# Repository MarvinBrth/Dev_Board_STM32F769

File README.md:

# Dev_Board_STM32F769
## Feature
- STM32F769BIT6
- OTG USB C FS
- OTG USB C HS
- DRAM
- DSI_Interface
- EMMC
### Infos
- Created with Kicad
- 6 Layer
- 5 x 5 cm
- Manufactorer: JLCPCB
- PCBA
  
## Blockdiagramm:

## Supply:

## STM32F769BIT6:

## USB_C_FS_OTG:

## USB_C_HS_OTG:

## EMMC:

## DSI_Interface:

## SDRAM:

## Layout:

## 3D-Model:

## Real life

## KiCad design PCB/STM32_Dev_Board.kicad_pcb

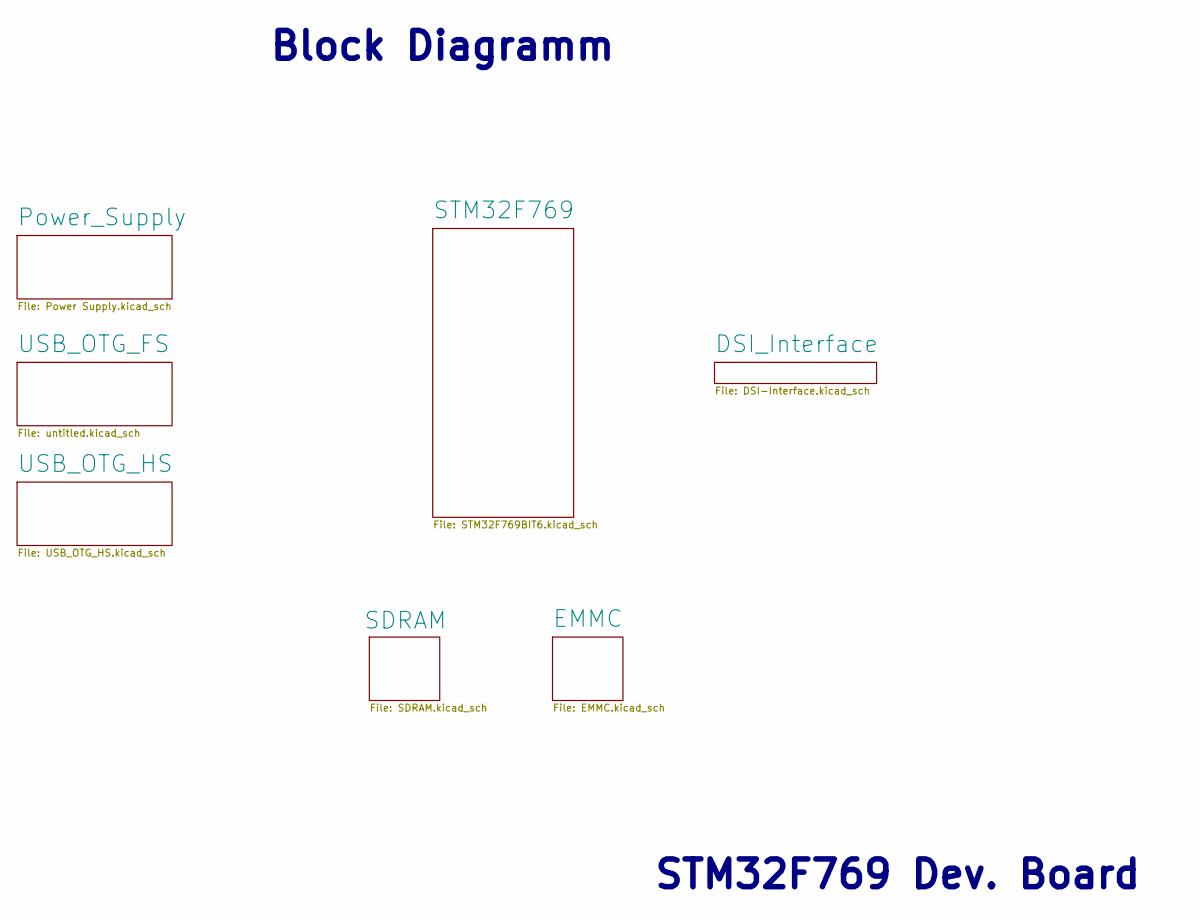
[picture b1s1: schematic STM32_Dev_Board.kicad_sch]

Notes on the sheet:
STM32F769 Dev. Board
Block Diagramm

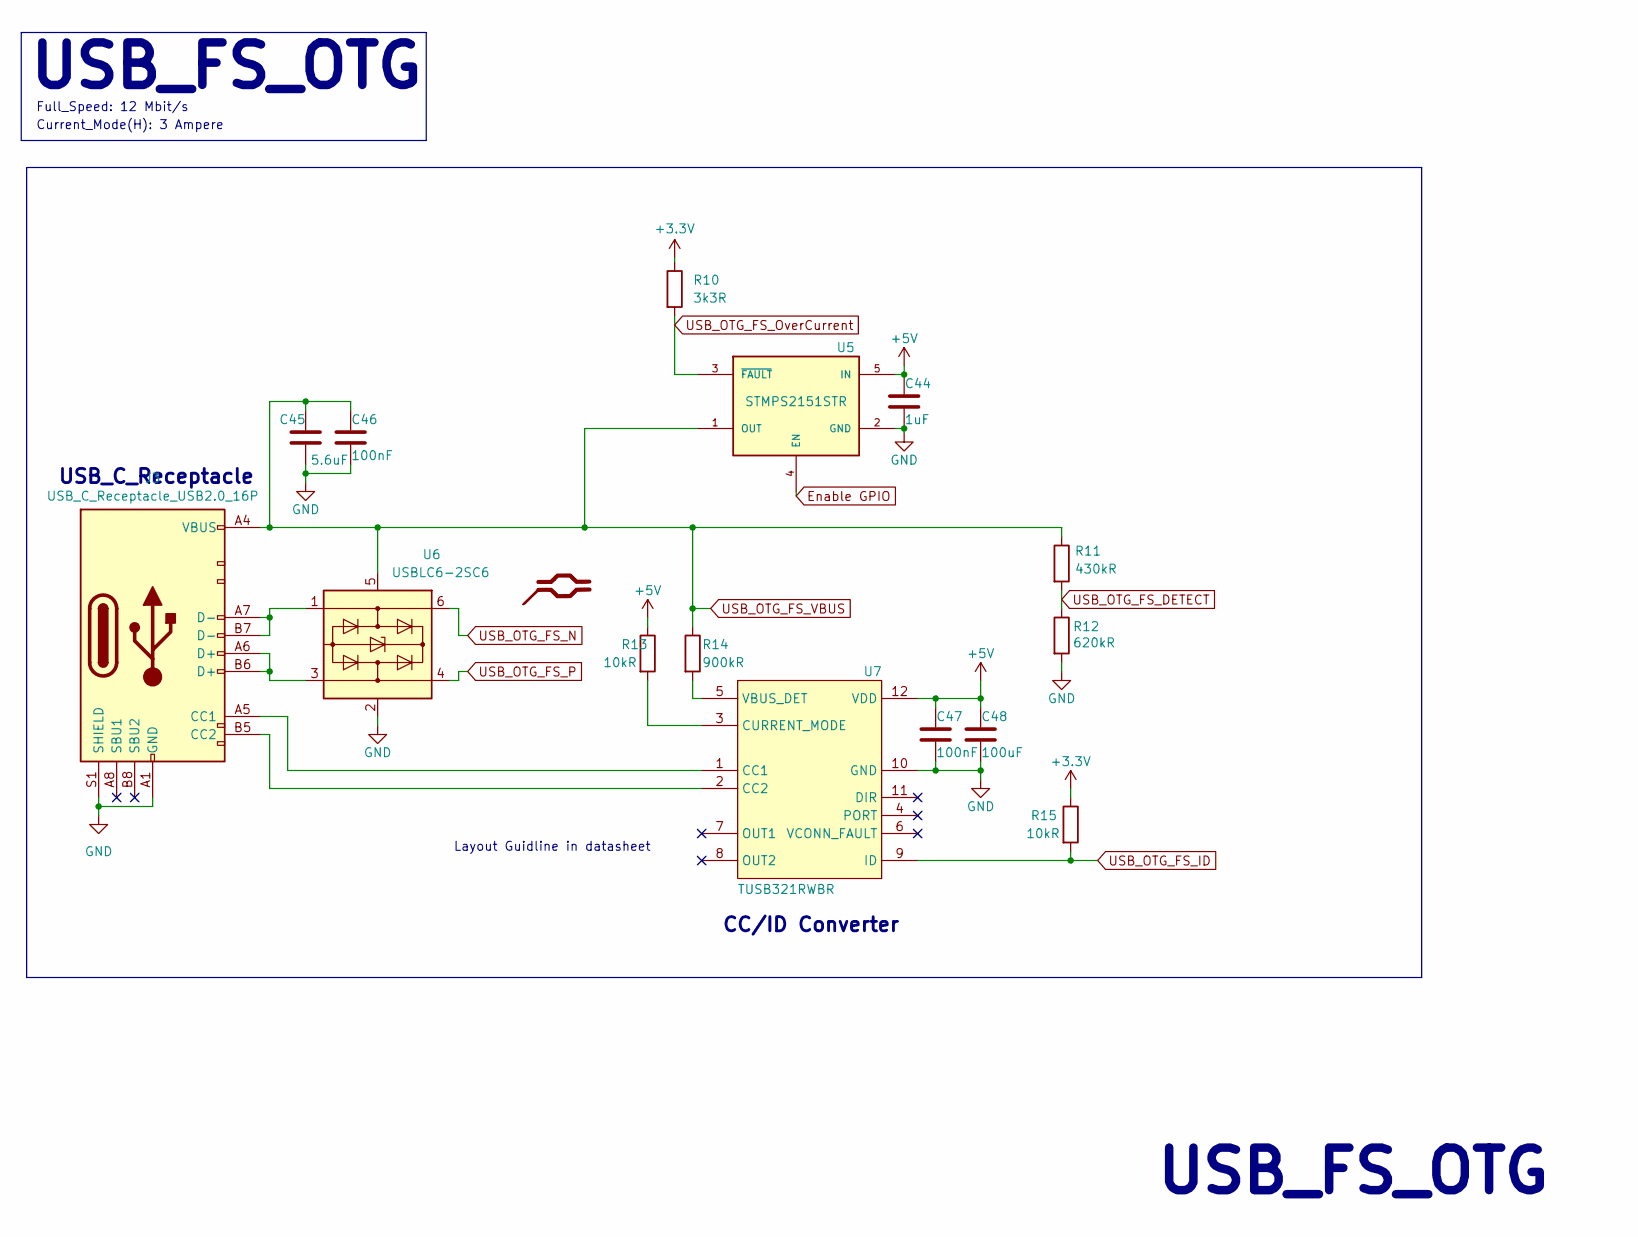
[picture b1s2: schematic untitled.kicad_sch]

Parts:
C44: 1uF; C_0603_1608Metric
C45: 5.6uF; C_0603_1608Metric
C46, C47: 100nF; C_0402_1005Metric
C48: 100uF; C_0805_2012Metric
J3: USB_C_Receptacle_USB2.0_16P; GT-USB-7047B_JLCPCB
R10: 3k3R; R_0402_1005Metric
R11: 430kR; R_0402_1005Metric
R12: 620kR; R_0402_1005Metric
R13, R15: 10kR; R_0402_1005Metric
R14: 900kR; R_0402_1005Metric
U5: STMPS2151STR; STMPS; PARTREV 7
U6: USBLC6-2SC6; SOT-23-6
U7: TUSB321RWBR

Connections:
+5V: C44.1, C47.1, C48.1, R13.1, U5.5 (IN), U7.12 (VDD); also elsewhere on the board
Enable GPIO: U5.4 (EN); also elsewhere on the board
GND: C44.2, C45.2, C46.2, C47.2, C48.2, J3.A1 (GND), J3.A12 (GND), J3.B1 (GND), J3.B12 (GND), J3.S1 (SHIELD), R12.2, U5.2 (GND), U6.2 (GND), U7.10 (GND); also elsewhere on the board
unnamed: J3.A5 (CC1), U7.1 (CC1)
unnamed: J3.B5 (CC2), U7.2 (CC2)
unnamed: J3.A6 (D+), J3.B6 (D+), U6.3 (I/O2)
unnamed: J3.A7 (D-), J3.B7 (D-), U6.1 (I/O1)
unnamed: R13.2, U7.3 (CURRENT_MODE)
unnamed: R14.2, U7.5 (VBUS_DET)
USB_OTG_FS_DETECT: R11.2, R12.1; also elsewhere on the board
USB_OTG_FS_ID: R15.2, U7.9 (ID); also elsewhere on the board
USB_OTG_FS_N: U6.6 (I/O1); also elsewhere on the board
USB_OTG_FS_OverCurrent: R10.2, U5.3 (~FAULT); also elsewhere on the board
USB_OTG_FS_P: U6.4 (I/O2); also elsewhere on the board
USB_OTG_FS_VBUS: C45.1, C46.1, J3.A4 (VBUS), J3.A9 (VBUS), J3.B4 (VBUS), J3.B9 (VBUS), R11.1, R14.1, U5.1 (OUT), U6.5 (VBUS); also elsewhere on the board
VDDSDMMC_STM32: R10.1, R15.1; also elsewhere on the board

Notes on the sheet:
Full_Speed: 12 Mbit/s
USB_FS_OTG
CC/ID Converter
Current_Mode(H): 3 Ampere
USB_C_Receptacle
Layout Guidline in datasheet

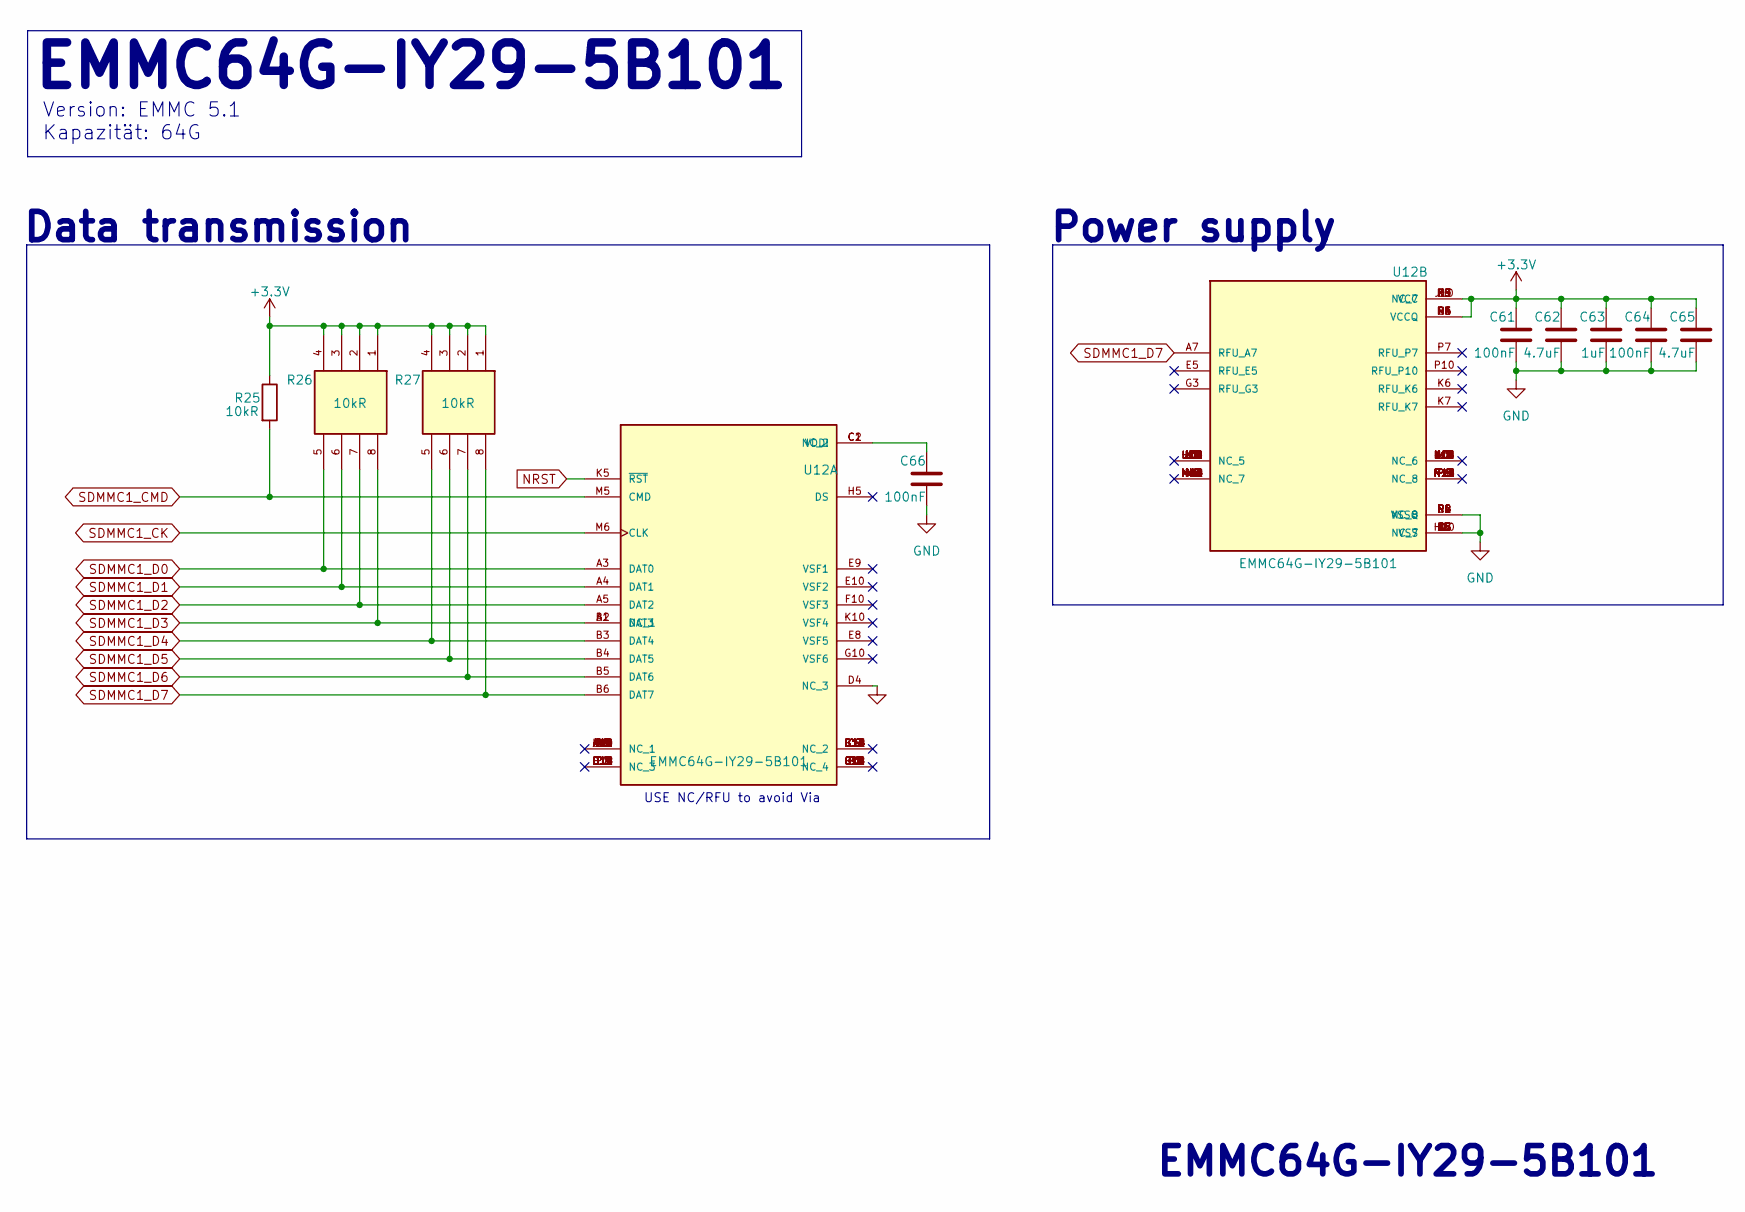
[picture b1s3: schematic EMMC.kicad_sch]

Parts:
C61, C64, C66: 100nF; C_0402_1005Metric
C62, C65: 4.7uF; C_0402_1005Metric
C63: 1uF; C_0402_1005Metric
R25: 10kR; R_0402_1005Metric
R26, R27: 10kR; Widerstandsarray_1; PARTREV 1-Mar-20
U12: EMMC64G-IY29-5B101; EMMC; PARTREV N/A

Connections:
GND: C61.2, C62.2, C63.2, C64.2, C65.2, C66.2, U12.A6 (VSS), U12.C4 (VSSQ), U12.D4 (NC_3), U12.E7 (VSS), U12.G5 (VSS), U12.H10 (VSS), U12.J5 (VSS), U12.K8 (VSS), U12.N2 (VSSQ), U12.N5 (VSSQ), U12.N6 (NC_7), U12.P2 (NC_8), U12.P4 (VSSQ), U12.P6 (VSSQ); also elsewhere on the board
NRST: U12.K5 (~RST); also elsewhere on the board
unnamed: C66.1, U12.C1 (NC_2), U12.C2 (VDDI)
SDMMC1_CK: U12.M6 (CLK); also elsewhere on the board
SDMMC1_CMD: R25.2, U12.M5 (CMD); also elsewhere on the board
SDMMC1_D0: R26.5, U12.A3 (DAT0); also elsewhere on the board
SDMMC1_D1: R26.6, U12.A4 (DAT1); also elsewhere on the board
SDMMC1_D2: R26.7, U12.A5 (DAT2); also elsewhere on the board
SDMMC1_D3: R26.8, U12.A1 (NC_1), U12.B2 (DAT3); also elsewhere on the board
SDMMC1_D4: R27.5, U12.A2 (NC_1), U12.B3 (DAT4); also elsewhere on the board
SDMMC1_D5: R27.6, U12.B4 (DAT5), U12.C3 (NC_2), U12.D1 (NC_3), U12.D2 (NC_3), U12.D3 (NC_3); also elsewhere on the board
SDMMC1_D6: R27.7, U12.B5 (DAT6), U12.C5 (NC_2); also elsewhere on the board
SDMMC1_D7: R27.8, U12.A7 (RFU_A7), U12.B6 (DAT7); also elsewhere on the board
VDDSDMMC_STM32: C61.1, C62.1, C63.1, C64.1, C65.1, R25.1, R26.1, R26.2, R26.3, R26.4, R27.1, R27.2, R27.3, R27.4, U12.C6 (VCCQ), U12.E6 (VCC), U12.F5 (VCC), U12.J10 (VCC), U12.K9 (VCC), U12.M4 (VCCQ), U12.N3 (NC_7), U12.N4 (VCCQ), U12.P3 (VCCQ), U12.P5 (VCCQ); also elsewhere on the board

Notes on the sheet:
USE NC/RFU to avoid Via
Data transmission
EMMC64G-IY29-5B101
Version: EMMC 5.1 Kapazität: 64G
Power supply

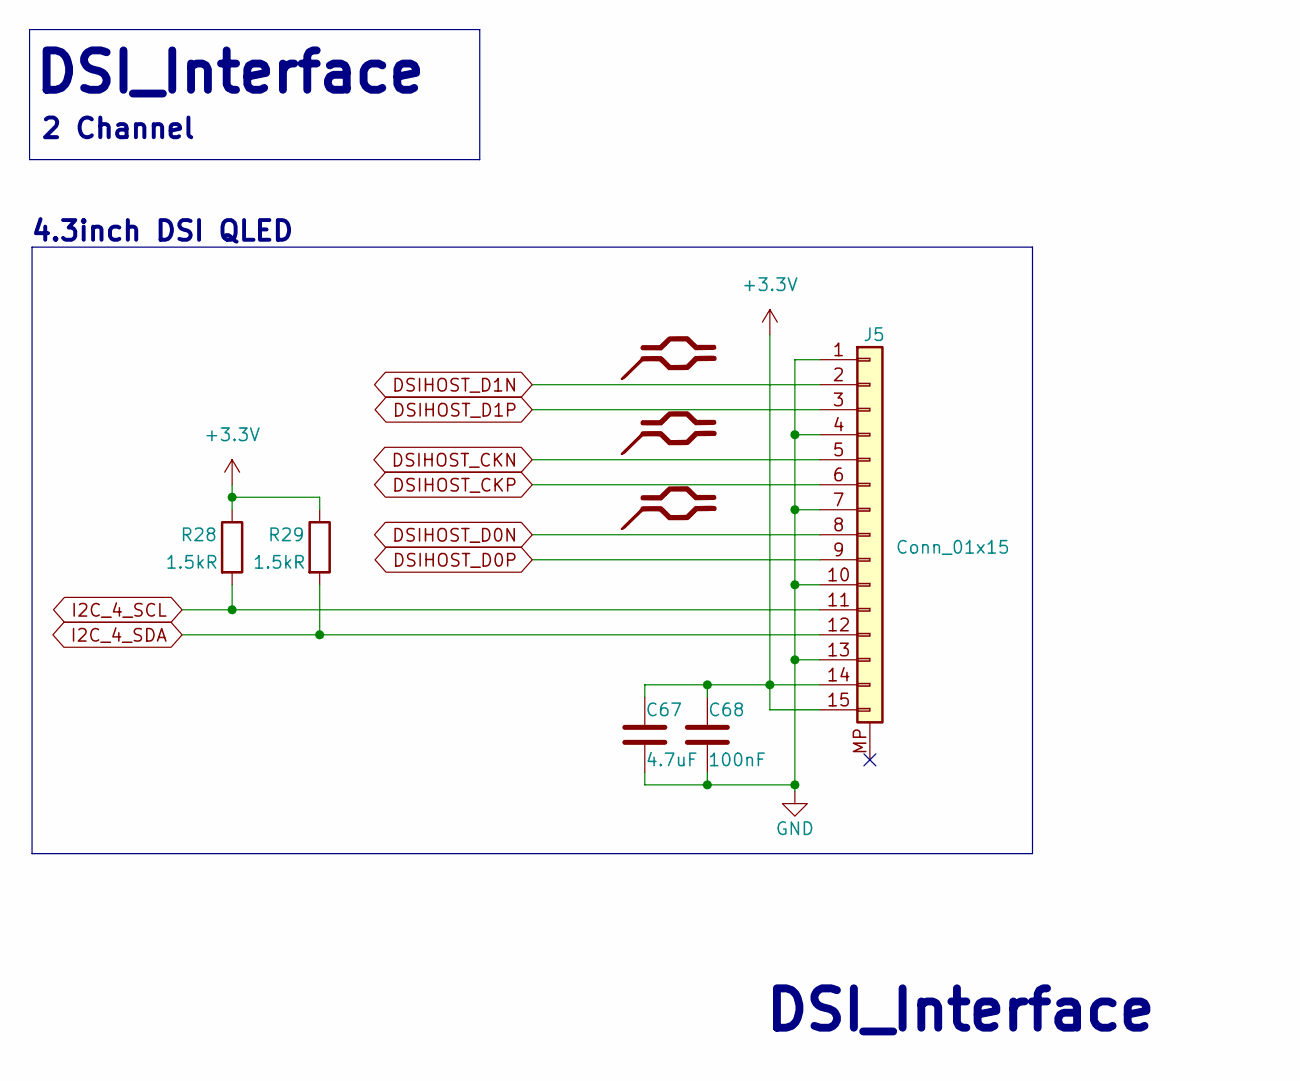
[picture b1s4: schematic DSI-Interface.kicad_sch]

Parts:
C67: 4.7uF; C_0603_1608Metric
C68: 100nF; C_0402_1005Metric
J5: Conn_01x15; TE_1-84952-5_1x15-1MP_P1.0mm_Horizontal
R28, R29: 1.5kR; R_0402_1005Metric

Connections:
DSIHOST_CKN: J5.5; also elsewhere on the board
DSIHOST_CKP: J5.6; also elsewhere on the board
DSIHOST_D0N: J5.8; also elsewhere on the board
DSIHOST_D0P: J5.9; also elsewhere on the board
DSIHOST_D1N: J5.2; also elsewhere on the board
DSIHOST_D1P: J5.3; also elsewhere on the board
GND: C67.2, C68.2, J5.1, J5.4, J5.7, J5.10, J5.13; also elsewhere on the board
I2C_4_SCL: J5.11, R28.2; also elsewhere on the board
I2C_4_SDA: J5.12, R29.2; also elsewhere on the board
VDDSDMMC_STM32: C67.1, C68.1, J5.14, J5.15, R28.1, R29.1; also elsewhere on the board

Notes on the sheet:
DSI_Interface
2 Channel
4.3inch DSI QLED

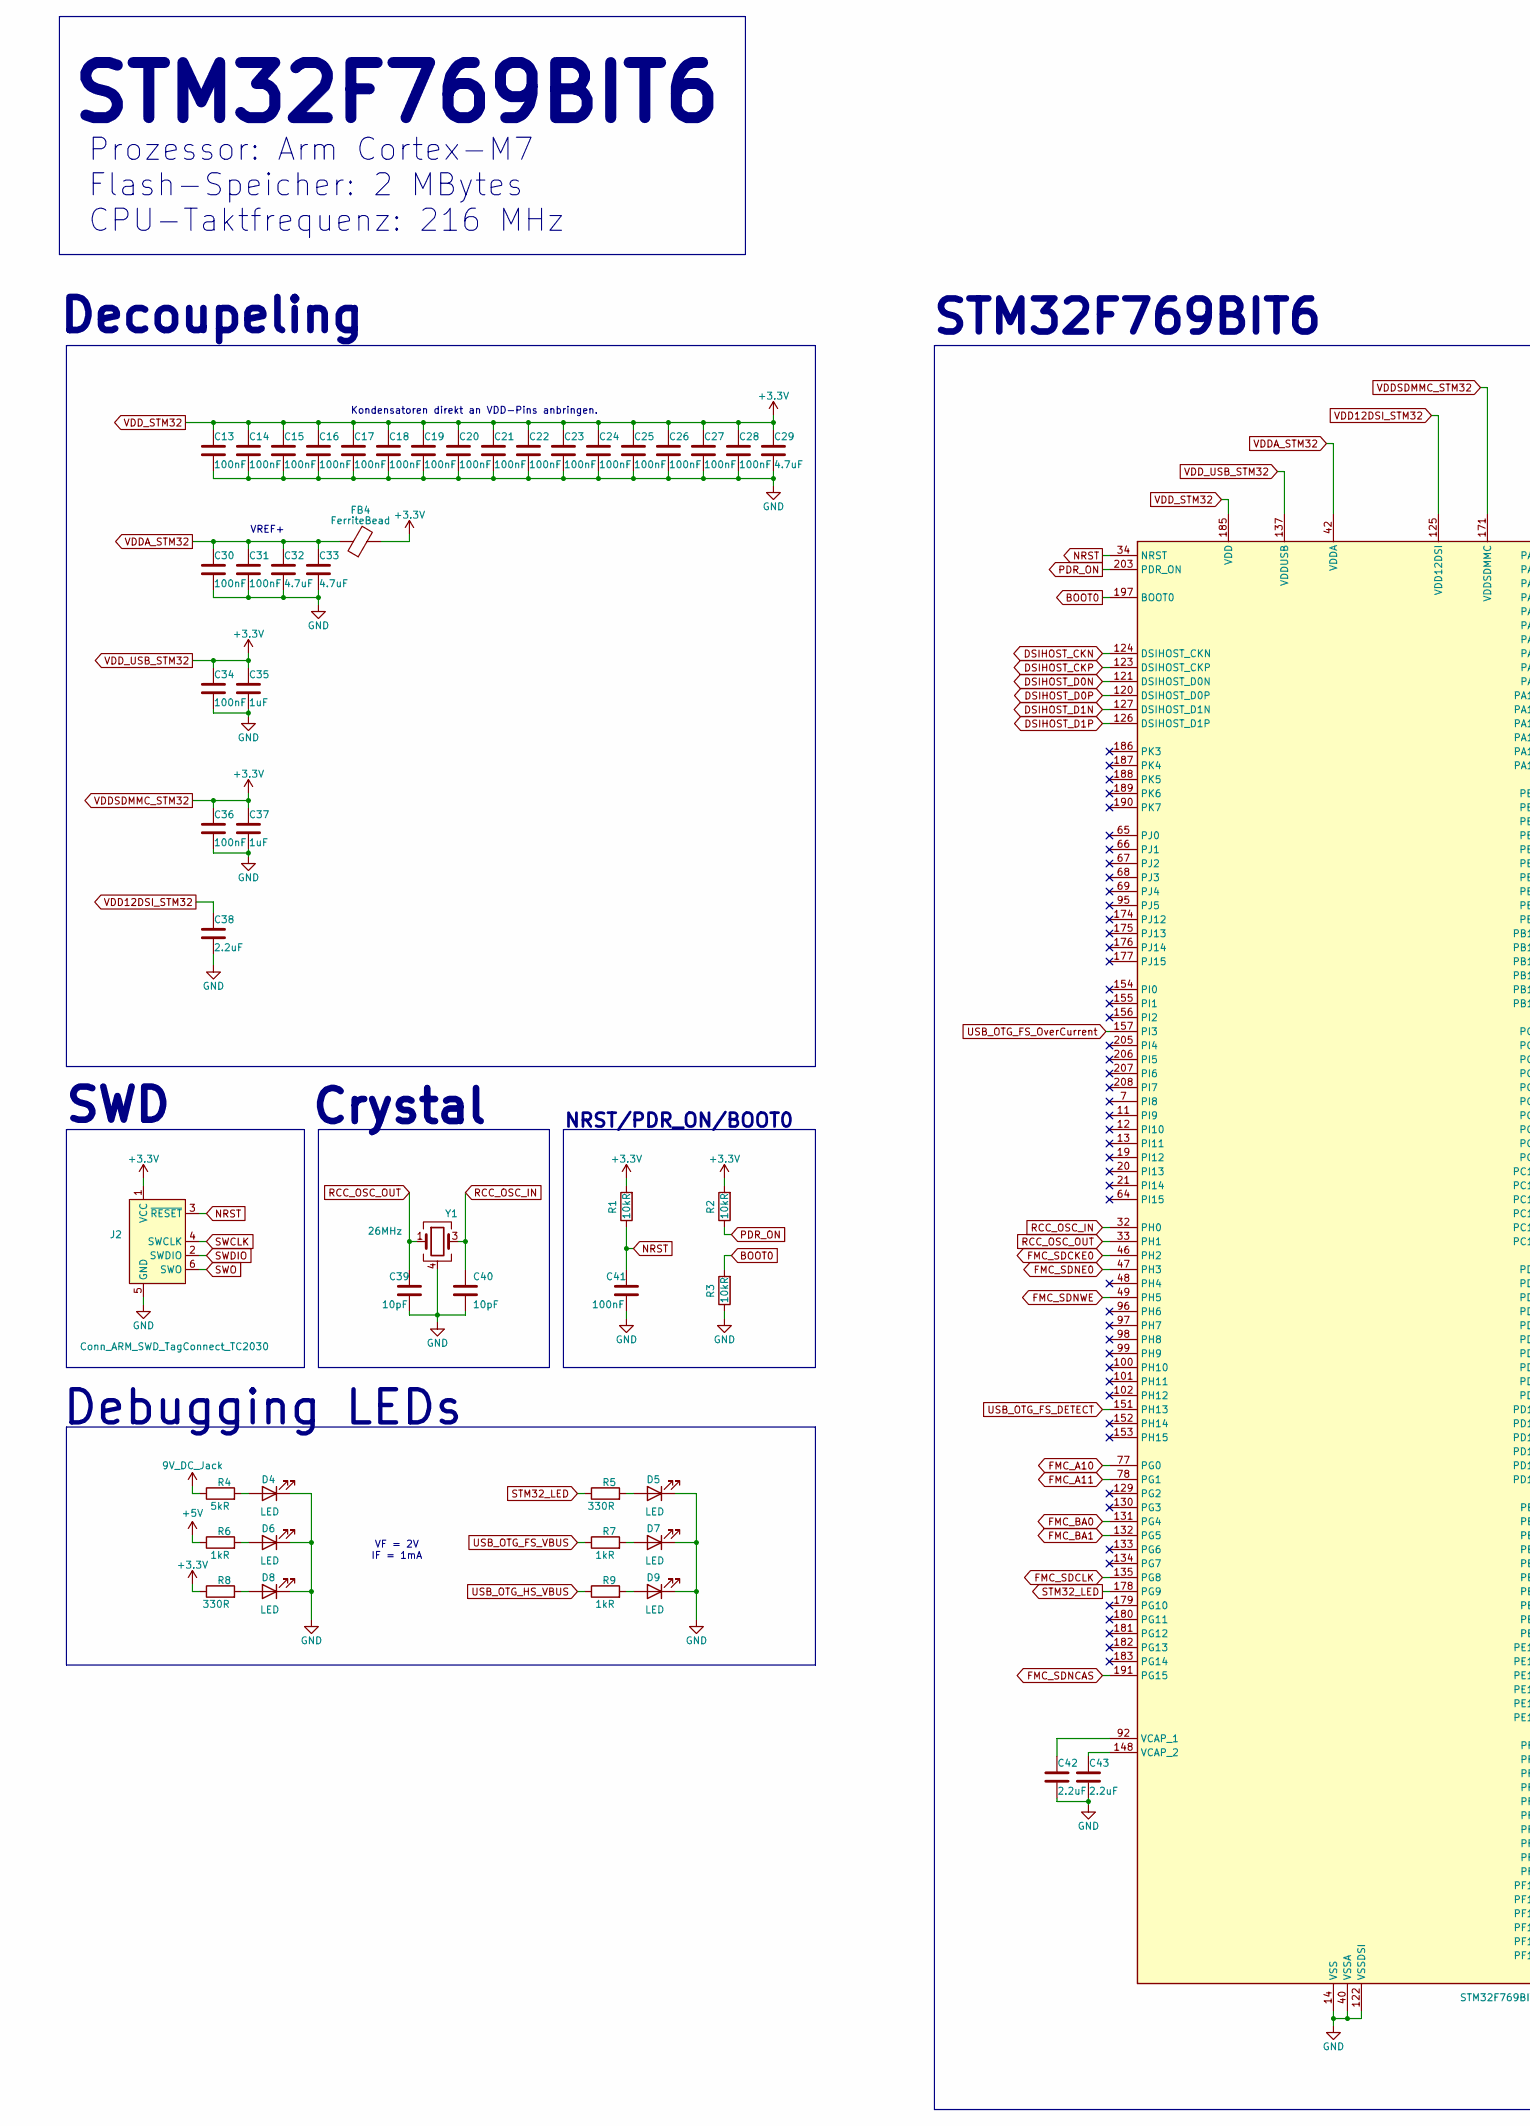
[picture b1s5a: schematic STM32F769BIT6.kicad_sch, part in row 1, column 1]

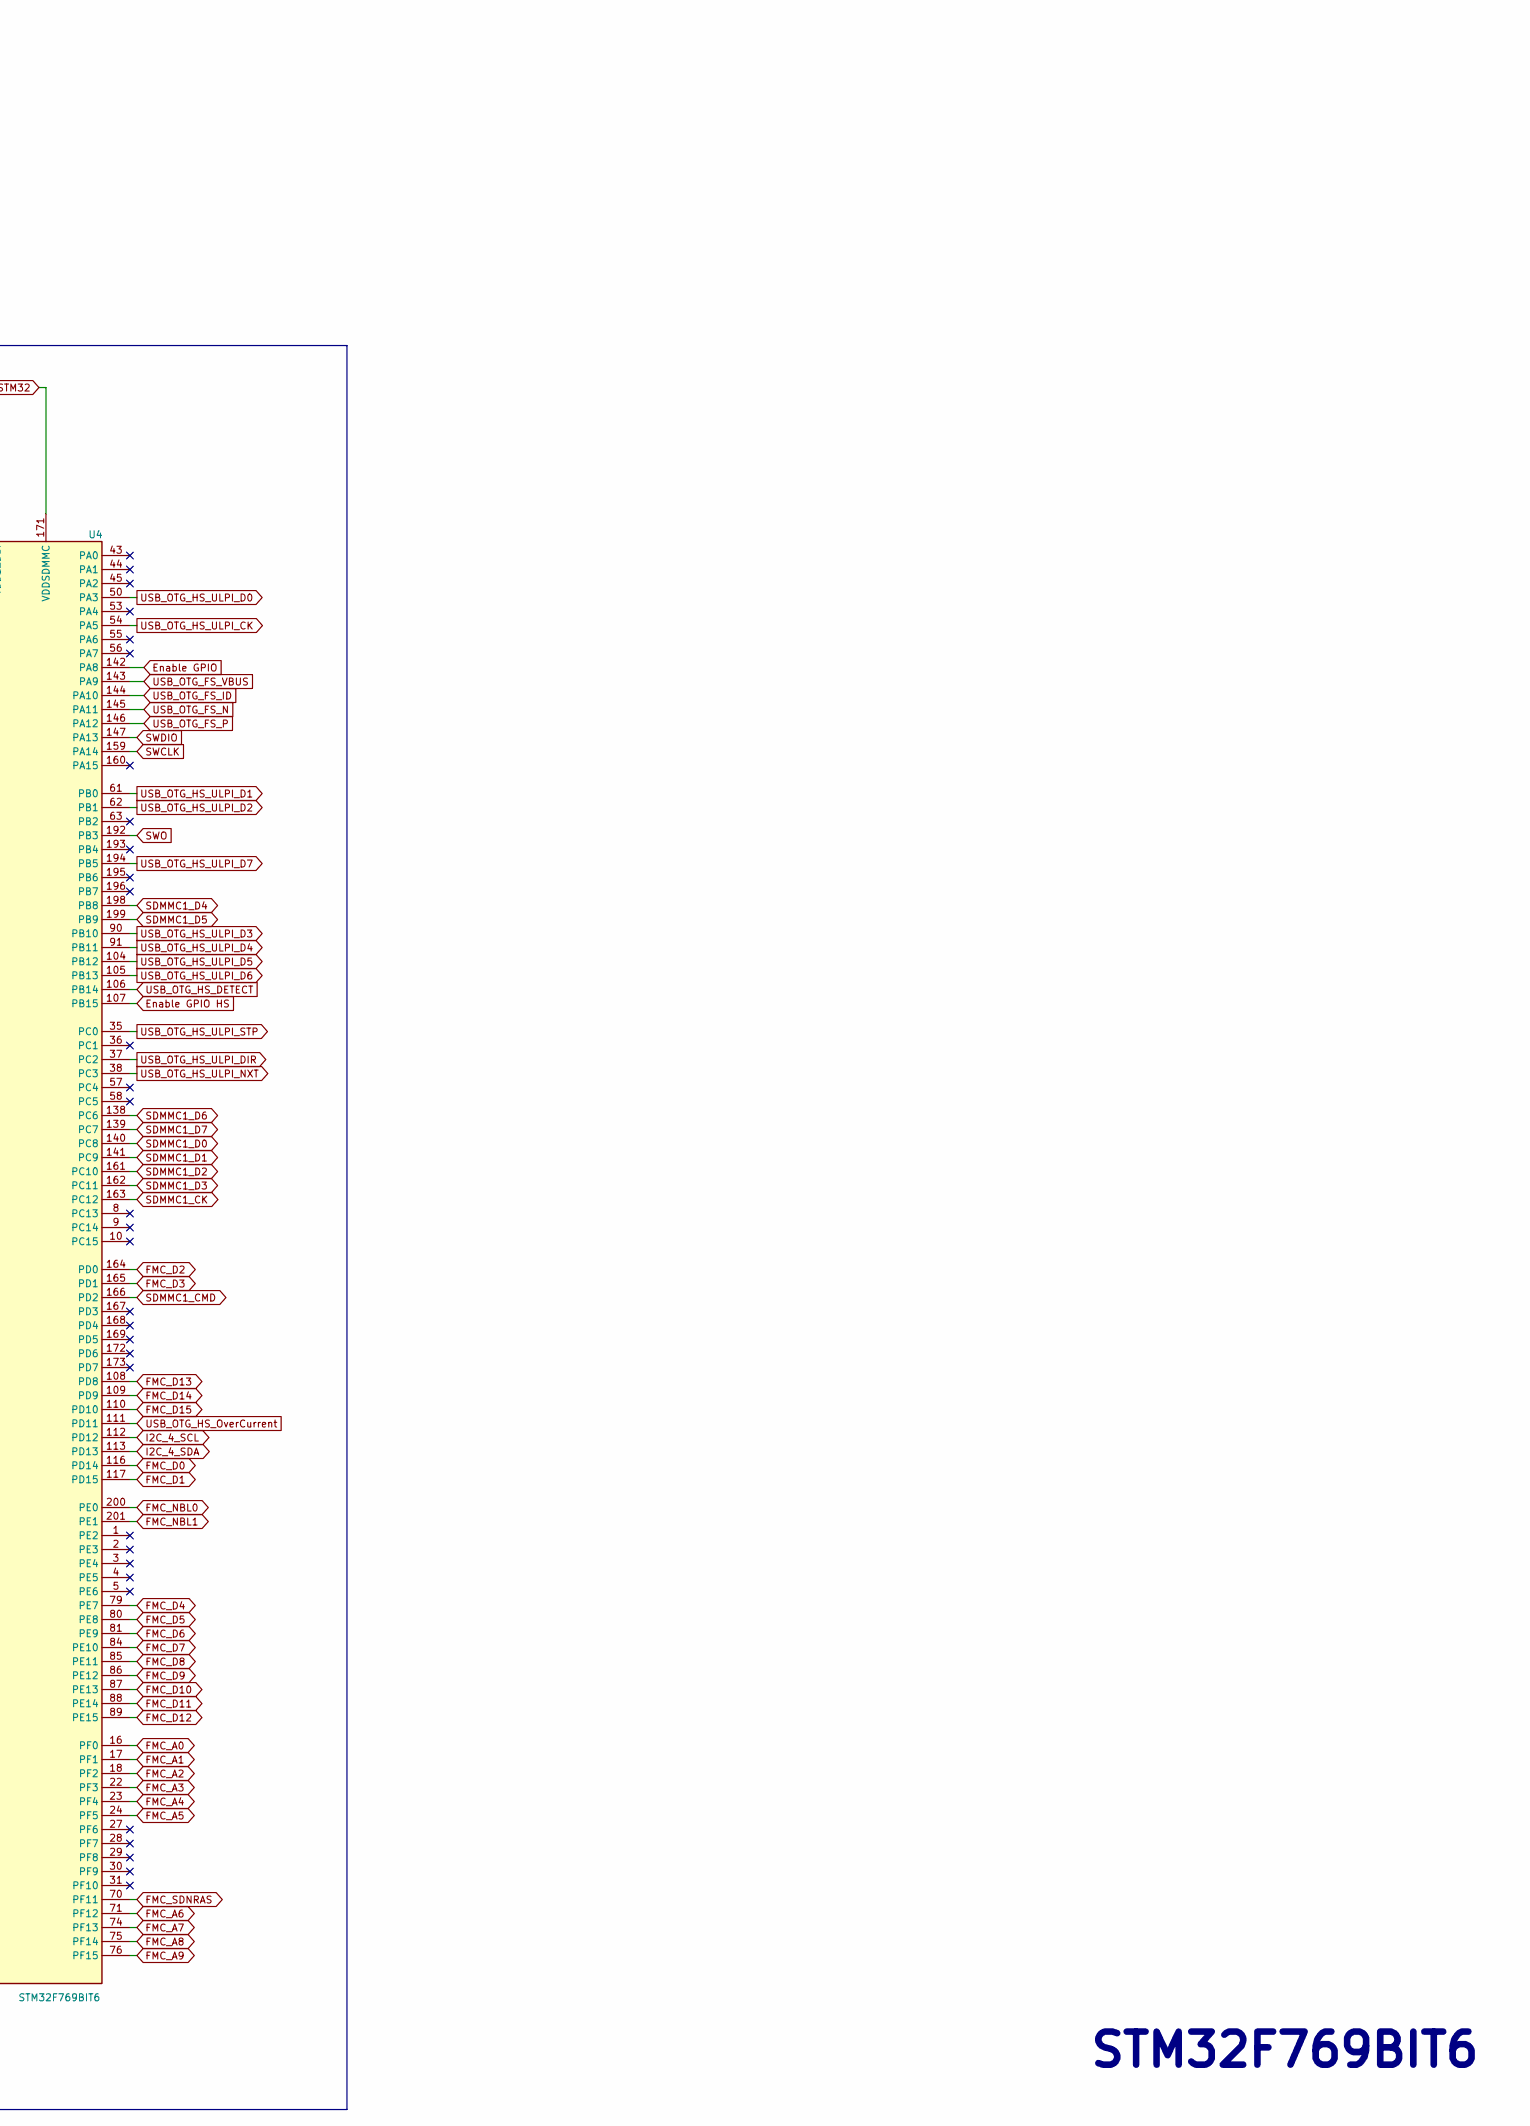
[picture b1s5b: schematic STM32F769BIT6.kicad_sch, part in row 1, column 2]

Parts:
C13, C14, C15, C16, C17, C18, C19, C20, C21, C22, C23, C24, C25, C26, C27, C28, C30, C31, C34, C36, C41: 100nF; C_0402_1005Metric
C29, C32, C33: 4.7uF; C_0603_1608Metric
C35, C37: 1uF; C_0603_1608Metric
C38, C42, C43: 2.2uF; C_0603_1608Metric
C39, C40: 10pF; C_0402_1005Metric
D4, D5, D6, D7, D8, D9: LED; LED_0603_1608Metric
FB4: FerriteBead; L_0603_1608Metric
J2: Conn_ARM_SWD_TagConnect_TC2030; Tag-Connect_TC2030-IDC-FP_2x03_P1.27mm_Vertical
R1, R2, R3: 10kR; R_0402_1005Metric
R4: 5kR; R_0402_1005Metric
R5, R8: 330R; R_0402_1005Metric
R6, R7, R9: 1kR; R_0402_1005Metric
U4: STM32F769BIT6; LQFP-208_28x28mm_P0.5mm
Y1: 26MHz; XTAL_ECS-240-10-36-CKM-TR

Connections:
9V_DC_Jack: R4.1; also elsewhere on the board
+5V: R6.1; also elsewhere on the board
BOOT0: R3.2, U4.197 (BOOT0)
DSIHOST_CKN: U4.124 (DSIHOST_CKN); also elsewhere on the board
DSIHOST_CKP: U4.123 (DSIHOST_CKP); also elsewhere on the board
DSIHOST_D0N: U4.121 (DSIHOST_D0N); also elsewhere on the board
DSIHOST_D0P: U4.120 (DSIHOST_D0P); also elsewhere on the board
DSIHOST_D1N: U4.127 (DSIHOST_D1N); also elsewhere on the board
DSIHOST_D1P: U4.126 (DSIHOST_D1P); also elsewhere on the board
Enable GPIO: U4.142 (PA8); also elsewhere on the board
Enable GPIO HS: U4.107 (PB15); also elsewhere on the board
FMC_A0: U4.16 (PF0); also elsewhere on the board
FMC_A1: U4.17 (PF1); also elsewhere on the board
FMC_A2: U4.18 (PF2); also elsewhere on the board
FMC_A3: U4.22 (PF3); also elsewhere on the board
FMC_A4: U4.23 (PF4); also elsewhere on the board
FMC_A5: U4.24 (PF5); also elsewhere on the board
FMC_A6: U4.71 (PF12); also elsewhere on the board
FMC_A7: U4.74 (PF13); also elsewhere on the board
FMC_A8: U4.75 (PF14); also elsewhere on the board
FMC_A9: U4.76 (PF15); also elsewhere on the board
FMC_A10: U4.77 (PG0); also elsewhere on the board
FMC_A11: U4.78 (PG1); also elsewhere on the board
FMC_BA0: U4.131 (PG4); also elsewhere on the board
FMC_BA1: U4.132 (PG5); also elsewhere on the board
FMC_D0: U4.116 (PD14); also elsewhere on the board
FMC_D1: U4.117 (PD15); also elsewhere on the board
FMC_D2: U4.164 (PD0); also elsewhere on the board
FMC_D3: U4.165 (PD1); also elsewhere on the board
FMC_D4: U4.79 (PE7); also elsewhere on the board
FMC_D5: U4.80 (PE8); also elsewhere on the board
FMC_D6: U4.81 (PE9); also elsewhere on the board
FMC_D7: U4.84 (PE10); also elsewhere on the board
FMC_D8: U4.85 (PE11); also elsewhere on the board
FMC_D9: U4.86 (PE12); also elsewhere on the board
FMC_D10: U4.87 (PE13); also elsewhere on the board
FMC_D11: U4.88 (PE14); also elsewhere on the board
FMC_D12: U4.89 (PE15); also elsewhere on the board
FMC_D13: U4.108 (PD8); also elsewhere on the board
FMC_D14: U4.109 (PD9); also elsewhere on the board
FMC_D15: U4.110 (PD10); also elsewhere on the board
FMC_NBL0: U4.200 (PE0); also elsewhere on the board
FMC_NBL1: U4.201 (PE1); also elsewhere on the board
FMC_SDCKE0: U4.46 (PH2); also elsewhere on the board
FMC_SDCLK: U4.135 (PG8); also elsewhere on the board
FMC_SDNCAS: U4.191 (PG15); also elsewhere on the board
FMC_SDNE0: U4.47 (PH3); also elsewhere on the board
FMC_SDNRAS: U4.70 (PF11); also elsewhere on the board
FMC_SDNWE: U4.49 (PH5); also elsewhere on the board
GND: C13.2, C14.2, C15.2, C16.2, C17.2, C18.2, C19.2, C20.2, C21.2, C22.2, C23.2, C24.2, C25.2, C26.2, C27.2, C28.2, C29.2, C30.2, C31.2, C32.2, C33.2, C34.2, C35.2, C36.2, C37.2, C38.2, C39.2, C40.2, C41.2, C42.2, C43.2, D4.1 (K), D5.1 (K), D6.1 (K), D7.1 (K), D8.1 (K), D9.1 (K), J2.5 (GND), R3.1, U4.14 (VSS), U4.25 (VSS), U4.40 (VSSA), U4.51 (VSS), U4.60 (VSS), U4.72 (VSS), U4.82 (VSS), U4.93 (VSS), U4.114 (VSS), U4.122 (VSSDSI), U4.128 (VSSDSI), U4.136 (VSS), U4.149 (VSS), U4.170 (VSS), U4.184 (VSS), U4.202 (VSS), Y1.2, Y1.4; also elsewhere on the board
I2C_4_SCL: U4.112 (PD12); also elsewhere on the board
I2C_4_SDA: U4.113 (PD13); also elsewhere on the board
NRST: C41.1, J2.3 (~RESET), R1.1, U4.34 (NRST); also elsewhere on the board
unnamed: D4.2 (A), R4.2
unnamed: D5.2 (A), R5.2
unnamed: D6.2 (A), R6.2
unnamed: D7.2 (A), R7.2
unnamed: D8.2 (A), R8.2
unnamed: D9.2 (A), R9.2
unnamed: C42.1, U4.92 (VCAP_1)
unnamed: C43.1, U4.148 (VCAP_2)
PDR_ON: R2.1, U4.203 (PDR_ON)
RCC_OSC_IN: C40.1, U4.32 (PH0), Y1.3
RCC_OSC_OUT: C39.1, U4.33 (PH1), Y1.1
SDMMC1_CK: U4.163 (PC12); also elsewhere on the board
SDMMC1_CMD: U4.166 (PD2); also elsewhere on the board
SDMMC1_D0: U4.140 (PC8); also elsewhere on the board
SDMMC1_D1: U4.141 (PC9); also elsewhere on the board
SDMMC1_D2: U4.161 (PC10); also elsewhere on the board
SDMMC1_D3: U4.162 (PC11); also elsewhere on the board
SDMMC1_D4: U4.198 (PB8); also elsewhere on the board
SDMMC1_D5: U4.199 (PB9); also elsewhere on the board
SDMMC1_D6: U4.138 (PC6); also elsewhere on the board
SDMMC1_D7: U4.139 (PC7); also elsewhere on the board
STM32_LED: R5.1, U4.178 (PG9)
SWCLK: J2.4 (SWCLK), U4.159 (PA14)
SWDIO: J2.2 (SWDIO), U4.147 (PA13)
SWO: J2.6 (SWO), U4.192 (PB3)
USB_OTG_FS_DETECT: U4.151 (PH13); also elsewhere on the board
USB_OTG_FS_ID: U4.144 (PA10); also elsewhere on the board
USB_OTG_FS_N: U4.145 (PA11); also elsewhere on the board
USB_OTG_FS_OverCurrent: U4.157 (PI3); also elsewhere on the board
USB_OTG_FS_P: U4.146 (PA12); also elsewhere on the board
USB_OTG_FS_VBUS: R7.1, U4.143 (PA9); also elsewhere on the board
USB_OTG_HS_DETECT: U4.106 (PB14); also elsewhere on the board
USB_OTG_HS_OverCurrent: U4.111 (PD11); also elsewhere on the board
USB_OTG_HS_ULPI_CK: U4.54 (PA5); also elsewhere on the board
USB_OTG_HS_ULPI_D0: U4.50 (PA3); also elsewhere on the board
USB_OTG_HS_ULPI_D1: U4.61 (PB0); also elsewhere on the board
USB_OTG_HS_ULPI_D2: U4.62 (PB1); also elsewhere on the board
USB_OTG_HS_ULPI_D3: U4.90 (PB10); also elsewhere on the board
USB_OTG_HS_ULPI_D4: U4.91 (PB11); also elsewhere on the board
USB_OTG_HS_ULPI_D5: U4.104 (PB12); also elsewhere on the board
USB_OTG_HS_ULPI_D6: U4.105 (PB13); also elsewhere on the board
USB_OTG_HS_ULPI_D7: U4.194 (PB5); also elsewhere on the board
USB_OTG_HS_ULPI_DIR: U4.37 (PC2); also elsewhere on the board
USB_OTG_HS_ULPI_NXT: U4.38 (PC3); also elsewhere on the board
USB_OTG_HS_ULPI_STP: U4.35 (PC0); also elsewhere on the board
USB_OTG_HS_VBUS: R9.1; also elsewhere on the board
VDD12DSI_STM32: C38.1, U4.119 (VCAPDSI), U4.125 (VDD12DSI)
VDDA_STM32: C30.1, C31.1, C32.1, C33.1, FB4.1, U4.41 (VREF+), U4.42 (VDDA)
VDDSDMMC_STM32: C13.1, C14.1, C15.1, C16.1, C17.1, C18.1, C19.1, C20.1, C21.1, C22.1, C23.1, C24.1, C25.1, C26.1, C27.1, C28.1, C29.1, C34.1, C35.1, C36.1, C37.1, FB4.2, J2.1 (VCC), R1.2, R2.2, R8.1, U4.6 (VBAT), U4.15 (VDD), U4.26 (VDD), U4.39 (VDD), U4.52 (VDD), U4.59 (VDD), U4.73 (VDD), U4.83 (VDD), U4.94 (VDD), U4.103 (VDD), U4.115 (VDD), U4.118 (VDDDSI), U4.137 (VDDUSB), U4.150 (VDD), U4.158 (VDD), U4.171 (VDDSDMMC), U4.185 (VDD), U4.204 (VDD); also elsewhere on the board

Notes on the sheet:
STM32F769BIT6
Decoupeling
STM32F769BIT6
Debugging LEDs
VF = 2V IF = 1mA
SWD
Kondensatoren direkt an VDD-Pins anbringen.
Crystal
NRST/PDR_ON/BOOT0
Prozessor: Arm Cortex-M7 Flash-Speicher: 2 MBytes CPU-Taktfrequenz: 216 MHz
VREF+
